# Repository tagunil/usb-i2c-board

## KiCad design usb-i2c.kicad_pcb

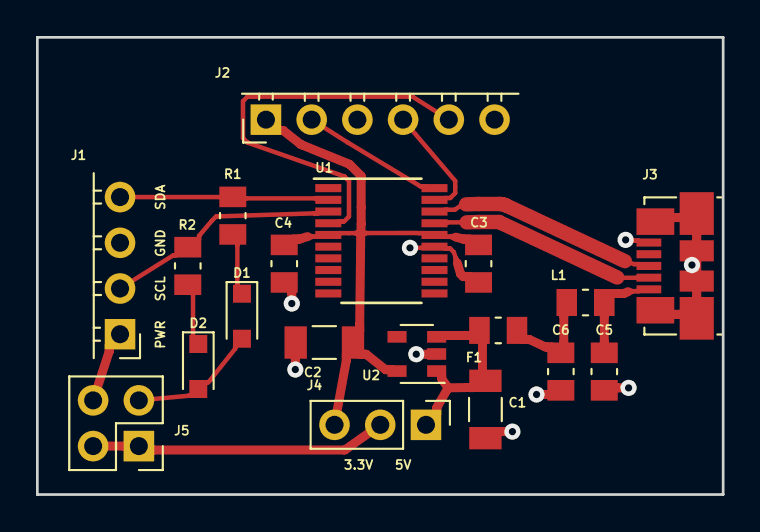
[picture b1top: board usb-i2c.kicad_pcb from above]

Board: 2 copper layers, 38.1 x 25.4 mm, 19 parts (0 on the bottom side), 17 nets.

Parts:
C1, C2: 4.7u; C_1206_3216Metric_Pad1.24x1.80mm_HandSolder
C3, C6: 100n; C_0805_2012Metric_Pad1.15x1.50mm_HandSolder
C4, C5: 10n; C_0805_2012Metric_Pad1.15x1.50mm_HandSolder
D1, D2: BAT60A; D_SOD-323_HandSoldering
F1: 500mA; Fuse_0805_2012Metric_Pad1.15x1.50mm_HandSolder
J1: I2C; PinSocket_1x04_P2.54mm_Horizontal
J2: SWD; PinHeader_1x06_P2.54mm_Horizontal
J3: USB; USB_Micro-B_Molex_47346-0001
J4: LEVEL; PinHeader_1x03_P2.54mm_Vertical
J5: POWER; PinHeader_2x02_P2.54mm_Vertical
L1: BLM21; L_0805_2012Metric_Pad1.15x1.50mm_HandSolder
R1, R2: 4.7k; R_0805_2012Metric_Pad1.15x1.50mm_HandSolder
U1: STM32F042F4Px; TSSOP-20_4.4x6.5mm_P0.65mm
U2: LD39015M33R; SOT-23-5

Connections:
+3V3: C2.1, C3.1, C4.1, J2.1, J4.3, U1.5, U1.16, U2.5
+5V: C1.1, F1.1, J4.1, U2.1, U2.3
/I2C_SCL: J1.2, R2.2, U1.3
/I2C_SDA: J1.4, R1.2, U1.2
/NRST: J2.5, U1.4
/SWCLK: J2.2, U1.20
/SWDIO: J2.4, U1.19
/USB_DM: J3.2, U1.17
/USB_DP: J3.3, U1.18
GND: C1.2, C2.2, C3.2, C4.2, C5.2, C6.2, J1.3, J2.3, J3.5, J3.6, U1.15, U2.2
unnamed: C5.1, J3.1, L1.1
unnamed: C6.1, F1.2, L1.2
unnamed: D1.1, R1.1
unnamed: D1.2, D2.2, J5.3
unnamed: D2.1, R2.1
unnamed: J1.1, J5.4
unnamed: J4.2, J5.1, J5.2

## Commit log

2018-05-24 Initial board revision.
2018-06-20 Remove stupid plotting path.
2018-06-21 Redraw MCU power lines.
2018-08-27 Fix connector model offset.
